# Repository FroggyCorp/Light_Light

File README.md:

# Light Light
It's a small PCB game with actually 2 games :

https://www.youtube.com/video/Cth2Q4qN7tQ/

https://www.youtube.com/video/z0U1Xu2ibLQ/

## The game

### How it work
Button 9 disable sound (horrible, i know)
Button 1 & 2 start game 1 or 2
All Button Player 1 & 2 at same time at the beggining reset highscore (little bit hard)

### Configuration
In light_light_func.h duree_jeu change the timeout of game1 2 = 20s
You can also change how many led will light at same time on game 1 with Jeu1_nombre_led_joueur_actif

### Game 1
You will have 4 LED, press button with led on as fast as you can until timeout of the game.

### Game 2
The program will add one led every x secondes, going faster and faster. It end when all the led are on for the two players.

## Game Board

Actually there is only dev board, which don't change so much. You can remove external connector to gain some place and make a smaller PCB.
It use an Attiny1604 & HT16K33A as it was the cheapest price and easy to use. Version with 75HC595 & 74HC595 may be a little bit cheaper but more difficult to make.
For Attiny1604, all reference on how to use it are[here]([https://pages.github.com/](https://github.com/SpenceKonde/AVR-Guidance/blob/master/UPDI/jtag2updi.md)) for UDPI & [here](https://github.com/SpenceKonde/megaTinyCore)
Thanks to [SpenceKonde](https://github.com/SpenceKonde) for his huge great work.

### Get notice
I use v1.1, v1.2 have some change and should work without problem.

### Information about the board
The board have 2 footprint for microphone, you need to get a passive one.
There are 2 foorprint for button + LED. One is cheap with standard 6x6mm tactil switch and 5730 LED, the other one use more expensive set with tactil switch & led in same package. You can take with [cap](https://www.lcsc.com/product-detail/Tactile-Switches_ROCPU-Switches-TPB01-101L1W_C2762125.html) or without and take that type of [cap] (https://www.lcsc.com/product-detail/Switch-Accessories-Caps_Khon-SC804AF1_C45359438.html). Be aware that some button + LED have cathode/anode at different position which will not work.
With 5730 LED, i recommend 5Kohm for R77 to R88 and 330ohm for the others.
You could also change the R for green LED.

### v1.2 :
- Correction Bug with Led J2 6-7-8-9
- Mutualising R for button
- Double footprint for microphone
- Change mounting hole
- Smaller PCB
- Add 5x220Ohm resistor to trick external battery cut off

## Small box

You can find .stl and FreeCad file inside FreeCad dir, as well as the PCB, i didn't try that version.

# Licence
Copyright (c) 2025 Froggy / FroggyCorp.

Do what you want with it until it's not money.

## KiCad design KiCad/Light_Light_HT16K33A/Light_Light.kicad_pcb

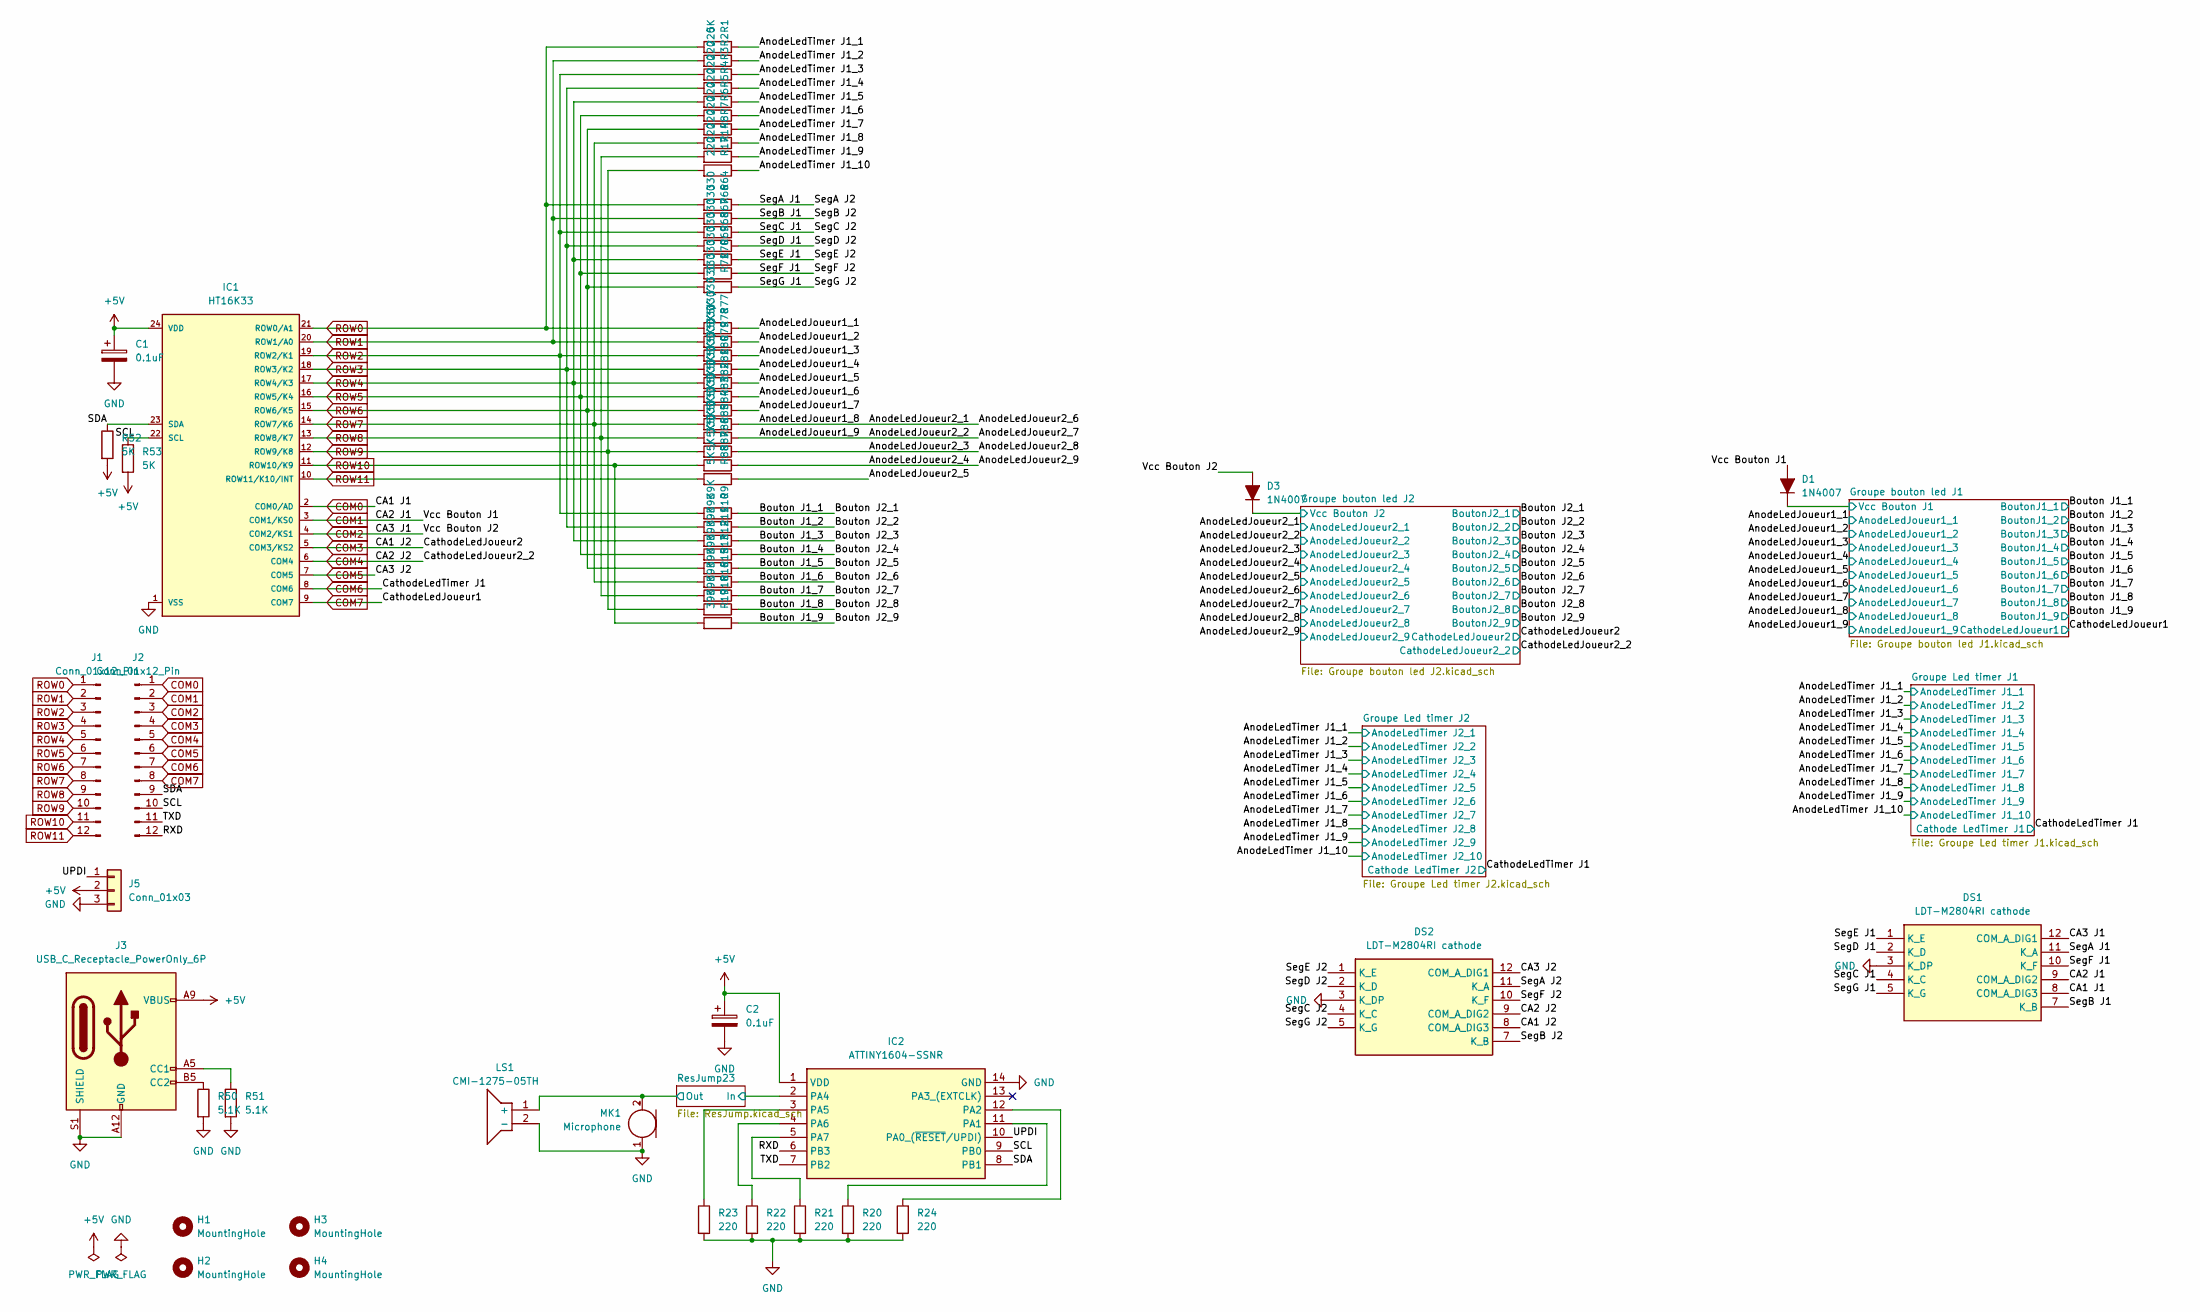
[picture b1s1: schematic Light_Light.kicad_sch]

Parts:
C1, C2: 0.1uF; C_0805_2012Metric_Pad1.15x1.40mm_HandSolder
D1, D3: 1N4007; D_DO-214AC_SMA; LCSC Part # C232439
DS1, DS2: LDT-M2804RI cathode; LDTM2804RI; Mouser Part Number 696-LDT-M2804RI
H1, H2, H3, H4: MountingHole; MountingHole_2.2mm_M2
IC1: HT16K33; LCSC Part # C5444736
IC2: ATTINY1604-SSNR; SOIC127P600X175-14N; Mouser Part Number 579-ATTINY1604-SSNR
J1, J2: Conn_01x12_Pin; PinHeader_1x12_P2.54mm_Vertical
J3: USB_C_Receptacle_PowerOnly_6P; USB_C_Receptacle_GCT_USB4125-xx-x_6P_TopMnt_Horizontal; LCSC Part # C668623
J5: Conn_01x03; PinHeader_1x03_P2.54mm_Horizontal; Part Number 1-0301FBV0T
LS1: CMI-1275-05TH; CMI127505TH; Mouser Part Number 179-CMI-1275-05TH
MK1: Microphone; POM-2244P-C3310-2-R; LCSC Part # C233957
R1, R52, R53: 5K; R_0805_2012Metric_Pad1.20x1.40mm_HandSolder
R2, R3, R4, R5, R6, R7, R8, R14, R17, R20, R21, R22, R23, R24: 220; R_0805_2012Metric_Pad1.20x1.40mm_HandSolder
R9, R10, R11, R12, R13, R15, R16, R18, R19: 39K; R_0805_2012Metric_Pad1.20x1.40mm_HandSolder
R50, R51: 5.1K; R_0805_2012Metric_Pad1.20x1.40mm_HandSolder
R64, R66, R67, R68, R69, R70, R71: 330; R_0805_2012Metric_Pad1.20x1.40mm_HandSolder
R77, R78, R79, R80, R81, R82, R83, R84, R85, R86, R87, R88: 5K / 330; R_0805_2012Metric_Pad1.20x1.40mm_HandSolder

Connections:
+5V: C1.1, C2.1, IC1.24 (VDD), IC2.1 (VDD), J3.A9 (VBUS), J3.B9 (VBUS), J5.2, R52.2, R53.2
/AnodeLedJoueur1_1: R77.1; also elsewhere on the board
/AnodeLedJoueur1_2: R78.1; also elsewhere on the board
/AnodeLedJoueur1_3: R79.1; also elsewhere on the board
/AnodeLedJoueur1_4: R80.1; also elsewhere on the board
/AnodeLedJoueur1_5: R81.1; also elsewhere on the board
/AnodeLedJoueur1_6: R82.1; also elsewhere on the board
/AnodeLedJoueur1_7: R83.1; also elsewhere on the board
/AnodeLedJoueur1_8: R84.1; also elsewhere on the board
/AnodeLedJoueur1_9: R85.1; also elsewhere on the board
/AnodeLedJoueur2_3: R86.1; also elsewhere on the board
/AnodeLedJoueur2_4: R87.1; also elsewhere on the board
/AnodeLedJoueur2_5: R88.1; also elsewhere on the board
/AnodeLedTimer J1_1: R1.1; also elsewhere on the board
/AnodeLedTimer J1_2: R2.1; also elsewhere on the board
/AnodeLedTimer J1_3: R3.1; also elsewhere on the board
/AnodeLedTimer J1_4: R4.1; also elsewhere on the board
/AnodeLedTimer J1_5: R5.1; also elsewhere on the board
/AnodeLedTimer J1_6: R6.1; also elsewhere on the board
/AnodeLedTimer J1_7: R7.1; also elsewhere on the board
/AnodeLedTimer J1_8: R8.1; also elsewhere on the board
/AnodeLedTimer J1_9: R14.1; also elsewhere on the board
/AnodeLedTimer J1_10: R17.1; also elsewhere on the board
/Bouton J1_1: R9.1; also elsewhere on the board
/Bouton J1_2: R10.1; also elsewhere on the board
/Bouton J1_3: R11.1; also elsewhere on the board
/Bouton J1_4: R12.1; also elsewhere on the board
/Bouton J1_5: R13.1; also elsewhere on the board
/Bouton J1_6: R15.1; also elsewhere on the board
/Bouton J1_7: R16.1; also elsewhere on the board
/Bouton J1_8: R18.1; also elsewhere on the board
/Bouton J1_9: R19.1; also elsewhere on the board
/Groupe bouton led J1/Vcc Bouton J1: D1.1 (K); also elsewhere on the board
/Groupe bouton led J2/Vcc Bouton J2: D3.1 (K); also elsewhere on the board
/RXD: IC2.6 (PB3), J2.12
/ResJump23/In: IC2.2 (PA4); also elsewhere on the board
/ResJump23/Out: LS1.1 (+), MK1.2 (+); also elsewhere on the board
/SCL: IC1.22 (SCL), IC2.9 (PB0), J2.10, R53.1
/SDA: IC1.23 (SDA), IC2.8 (PB1), J2.9, R52.1
/SegA J1: DS1.11 (K_A), DS2.11 (K_A), R64.1
/SegB J1: DS1.7 (K_B), DS2.7 (K_B), R66.1
/SegC J1: DS1.4 (K_C), DS2.4 (K_C), R67.1
/SegD J1: DS1.2 (K_D), DS2.2 (K_D), R68.1
/SegE J1: DS1.1 (K_E), DS2.1 (K_E), R69.1
/SegF J1: DS1.10 (K_F), DS2.10 (K_F), R70.1
/SegG J1: DS1.5 (K_G), DS2.5 (K_G), R71.1
/TXD: IC2.7 (PB2), J2.11
/UPDI: IC2.10 (PA0_(~RESET/UPDI)), J5.1
COM0: DS1.8 (COM_A_DIG3), IC1.2 (COM0/AD), J2.1
COM1: D1.2 (A), DS1.9 (COM_A_DIG2), IC1.3 (COM1/KS0), J2.2
COM2: D3.2 (A), DS1.12 (COM_A_DIG1), IC1.4 (COM2/KS1), J2.3
COM3: DS2.8 (COM_A_DIG3), IC1.5 (COM3/KS2), J2.4; also elsewhere on the board
COM4: DS2.9 (COM_A_DIG2), IC1.6 (COM4), J2.5; also elsewhere on the board
COM5: DS2.12 (COM_A_DIG1), IC1.7 (COM5), J2.6
COM6: IC1.8 (COM6), J2.7; also elsewhere on the board
COM7: IC1.9 (COM7), J2.8; also elsewhere on the board
GND: C1.2, C2.2, DS1.3 (K_DP), DS2.3 (K_DP), IC1.1 (VSS), IC2.14 (GND), J3.A12 (GND), J3.B12 (GND), J3.S1 (SHIELD), J5.3, LS1.2 (-), MK1.1 (-), R20.2, R21.2, R22.2, R23.2, R24.2, R50.2, R51.2
unnamed: IC2.11 (PA1), R20.1
unnamed: IC2.12 (PA2), R24.1
unnamed: IC2.3 (PA5), R23.1
unnamed: IC2.4 (PA6), R22.1
unnamed: IC2.5 (PA7), R21.1
unnamed: J3.A5 (CC1), R51.1
unnamed: J3.B5 (CC2), R50.1
ROW0: IC1.21 (ROW0/A1), J1.1, R1.2, R64.2, R77.2
ROW1: IC1.20 (ROW1/A0), J1.2, R2.2, R66.2, R78.2
ROW2: IC1.19 (ROW2/K1), J1.3, R3.2, R9.2, R67.2, R79.2
ROW3: IC1.18 (ROW3/K2), J1.4, R4.2, R10.2, R68.2, R80.2
ROW4: IC1.17 (ROW4/K3), J1.5, R5.2, R11.2, R69.2, R81.2
ROW5: IC1.16 (ROW5/K4), J1.6, R6.2, R12.2, R70.2, R82.2
ROW6: IC1.15 (ROW6/K5), J1.7, R7.2, R13.2, R71.2, R83.2
ROW7: IC1.14 (ROW7/K6), J1.8, R8.2, R15.2, R84.2
ROW8: IC1.13 (ROW8/K7), J1.9, R14.2, R16.2, R85.2
ROW9: IC1.12 (ROW9/K8), J1.10, R17.2, R18.2, R86.2
ROW10: IC1.11 (ROW10/K9), J1.11, R19.2, R87.2
ROW11: IC1.10 (ROW11/K10/INT), J1.12, R88.2

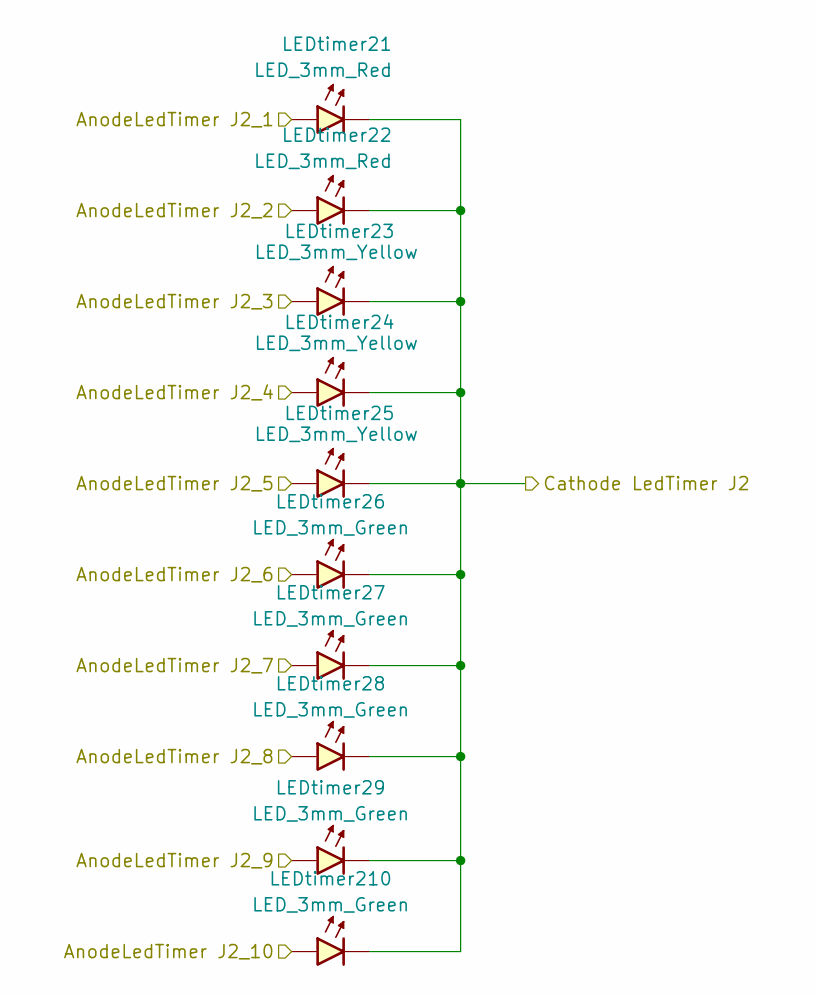
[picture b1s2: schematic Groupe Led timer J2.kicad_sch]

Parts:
LEDtimer21, LEDtimer22: LED_3mm_Red; LED_D3.0mm; LCSC Part # C84774
LEDtimer23, LEDtimer24, LEDtimer25: LED_3mm_Yellow; LED_D3.0mm; LCSC Part # C2895472
LEDtimer26, LEDtimer27, LEDtimer28, LEDtimer29, LEDtimer210: LED_3mm_Green; LED_D3.0mm; LCSC Part # C5907154

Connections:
/AnodeLedTimer J1_1: LEDtimer21.2 (A); also elsewhere on the board
/AnodeLedTimer J1_2: LEDtimer22.2 (A); also elsewhere on the board
/AnodeLedTimer J1_3: LEDtimer23.2 (A); also elsewhere on the board
/AnodeLedTimer J1_4: LEDtimer24.2 (A); also elsewhere on the board
/AnodeLedTimer J1_5: LEDtimer25.2 (A); also elsewhere on the board
/AnodeLedTimer J1_6: LEDtimer26.2 (A); also elsewhere on the board
/AnodeLedTimer J1_7: LEDtimer27.2 (A); also elsewhere on the board
/AnodeLedTimer J1_8: LEDtimer28.2 (A); also elsewhere on the board
/AnodeLedTimer J1_9: LEDtimer29.2 (A); also elsewhere on the board
/AnodeLedTimer J1_10: LEDtimer210.2 (A); also elsewhere on the board
COM6: LEDtimer21.1 (K), LEDtimer22.1 (K), LEDtimer23.1 (K), LEDtimer24.1 (K), LEDtimer25.1 (K), LEDtimer26.1 (K), LEDtimer27.1 (K), LEDtimer28.1 (K), LEDtimer29.1 (K), LEDtimer210.1 (K); also elsewhere on the board

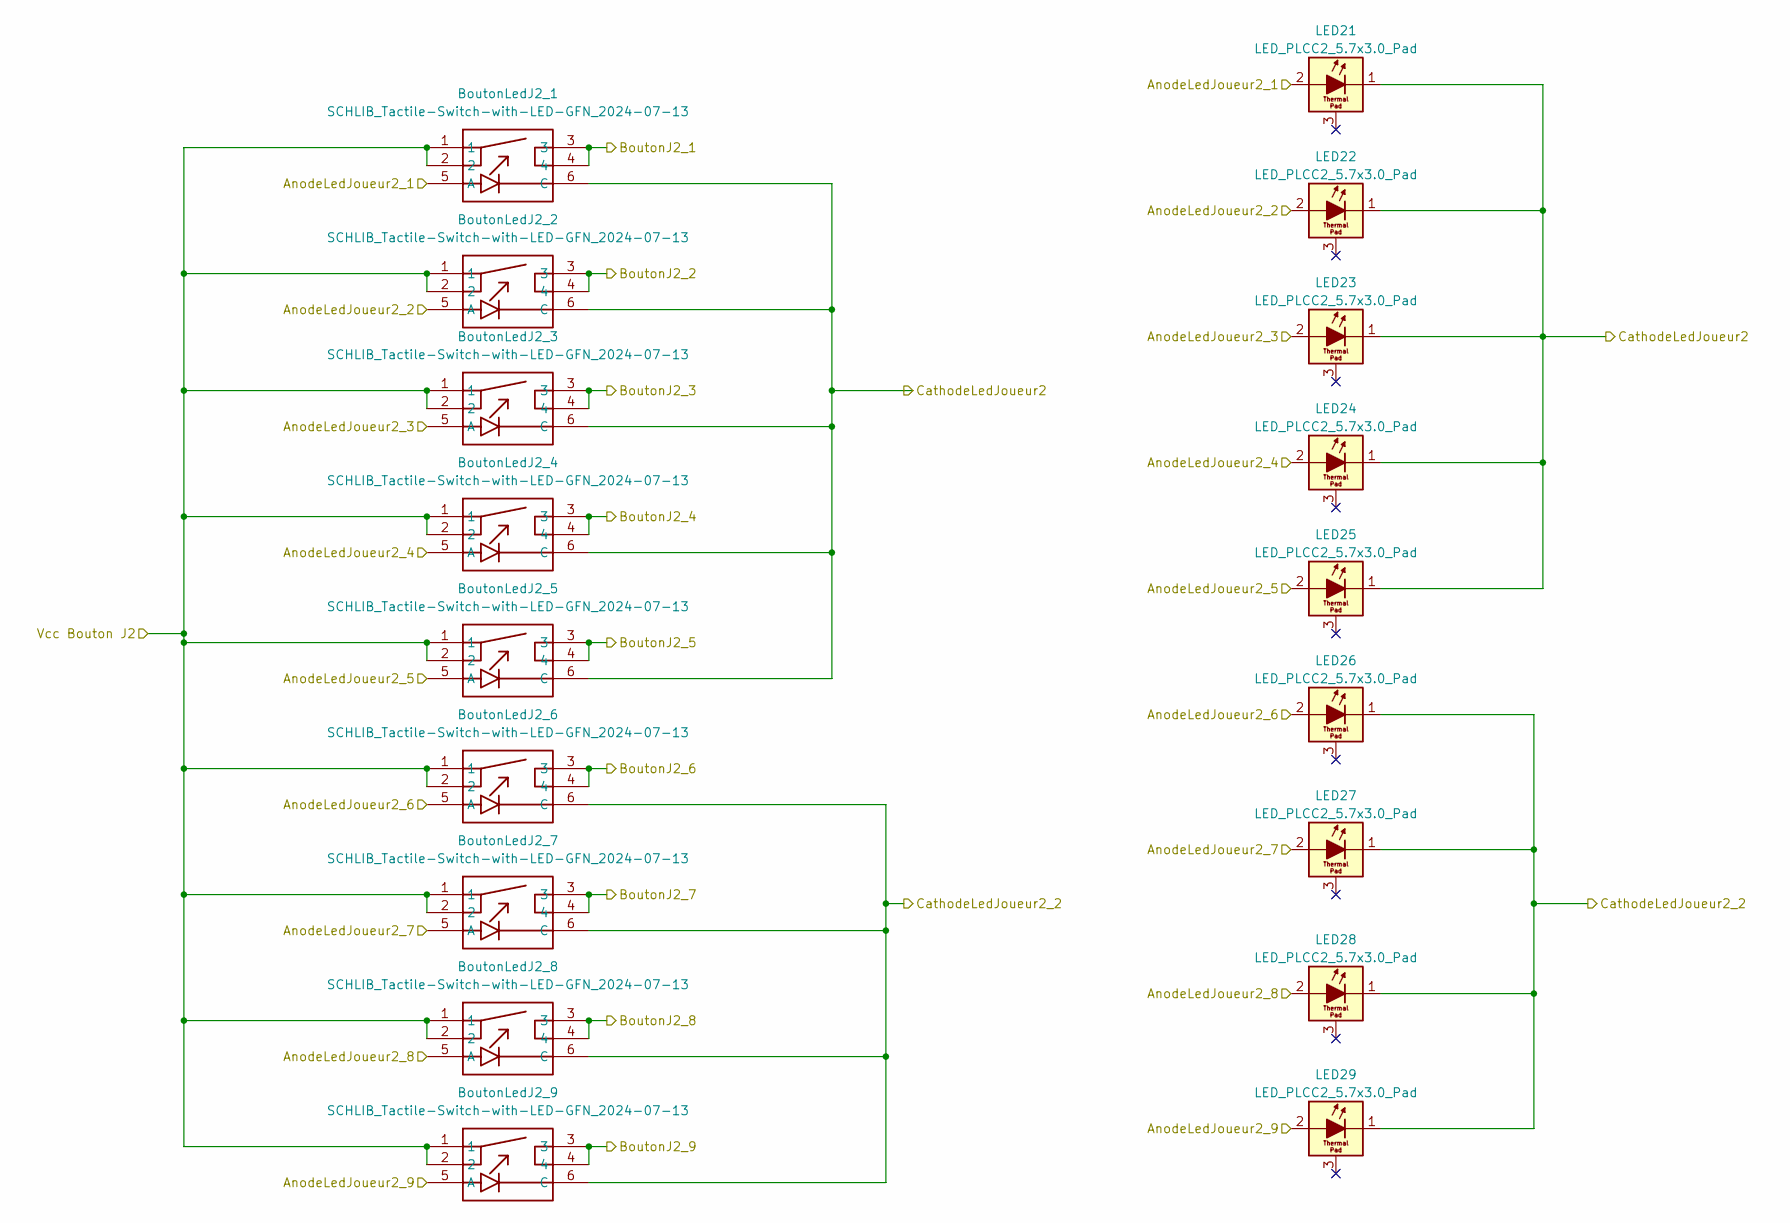
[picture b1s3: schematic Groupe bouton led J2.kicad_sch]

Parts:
BoutonLedJ2_1, BoutonLedJ2_2, BoutonLedJ2_3, BoutonLedJ2_4, BoutonLedJ2_5, BoutonLedJ2_6, BoutonLedJ2_7, BoutonLedJ2_8, BoutonLedJ2_9: SCHLIB_Tactile-Switch-with-LED-GFN_2024-07-13; 6MM SWITCH WITH LED GFN; Manufacturer Part New SchematicLib; LCSC Part # C354964
LED21, LED22, LED23, LED24, LED25, LED26, LED27, LED28, LED29: LED_PLCC2_5.7x3.0_Pad; LED_Yuji_5730

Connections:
/AnodeLedJoueur1_8: BoutonLedJ2_1.5 (A), BoutonLedJ2_6.5 (A), LED21.2 (A), LED26.2 (A); also elsewhere on the board
/AnodeLedJoueur1_9: BoutonLedJ2_2.5 (A), BoutonLedJ2_7.5 (A), LED22.2 (A), LED27.2 (A); also elsewhere on the board
/AnodeLedJoueur2_3: BoutonLedJ2_3.5 (A), BoutonLedJ2_8.5 (A), LED23.2 (A), LED28.2 (A); also elsewhere on the board
/AnodeLedJoueur2_4: BoutonLedJ2_4.5 (A), BoutonLedJ2_9.5 (A), LED24.2 (A), LED29.2 (A); also elsewhere on the board
/AnodeLedJoueur2_5: BoutonLedJ2_5.5 (A), LED25.2 (A); also elsewhere on the board
/Bouton J1_1: BoutonLedJ2_1.3, BoutonLedJ2_1.4; also elsewhere on the board
/Bouton J1_2: BoutonLedJ2_2.3, BoutonLedJ2_2.4; also elsewhere on the board
/Bouton J1_3: BoutonLedJ2_3.3, BoutonLedJ2_3.4; also elsewhere on the board
/Bouton J1_4: BoutonLedJ2_4.3, BoutonLedJ2_4.4; also elsewhere on the board
/Bouton J1_5: BoutonLedJ2_5.3, BoutonLedJ2_5.4; also elsewhere on the board
/Bouton J1_6: BoutonLedJ2_6.3, BoutonLedJ2_6.4; also elsewhere on the board
/Bouton J1_7: BoutonLedJ2_7.3, BoutonLedJ2_7.4; also elsewhere on the board
/Bouton J1_8: BoutonLedJ2_8.3, BoutonLedJ2_8.4; also elsewhere on the board
/Bouton J1_9: BoutonLedJ2_9.3, BoutonLedJ2_9.4; also elsewhere on the board
/Groupe bouton led J2/Vcc Bouton J2: BoutonLedJ2_1.1, BoutonLedJ2_1.2, BoutonLedJ2_2.1, BoutonLedJ2_2.2, BoutonLedJ2_3.1, BoutonLedJ2_3.2, BoutonLedJ2_4.1, BoutonLedJ2_4.2, BoutonLedJ2_5.1, BoutonLedJ2_5.2, BoutonLedJ2_6.1, BoutonLedJ2_6.2, BoutonLedJ2_7.1, BoutonLedJ2_7.2, BoutonLedJ2_8.1, BoutonLedJ2_8.2, BoutonLedJ2_9.1, BoutonLedJ2_9.2; also elsewhere on the board
COM3: BoutonLedJ2_1.6 (C), BoutonLedJ2_2.6 (C), BoutonLedJ2_3.6 (C), BoutonLedJ2_4.6 (C), BoutonLedJ2_5.6 (C), LED21.1 (K), LED22.1 (K), LED23.1 (K), LED24.1 (K), LED25.1 (K); also elsewhere on the board
COM4: BoutonLedJ2_6.6 (C), BoutonLedJ2_7.6 (C), BoutonLedJ2_8.6 (C), BoutonLedJ2_9.6 (C), LED26.1 (K), LED27.1 (K), LED28.1 (K), LED29.1 (K); also elsewhere on the board

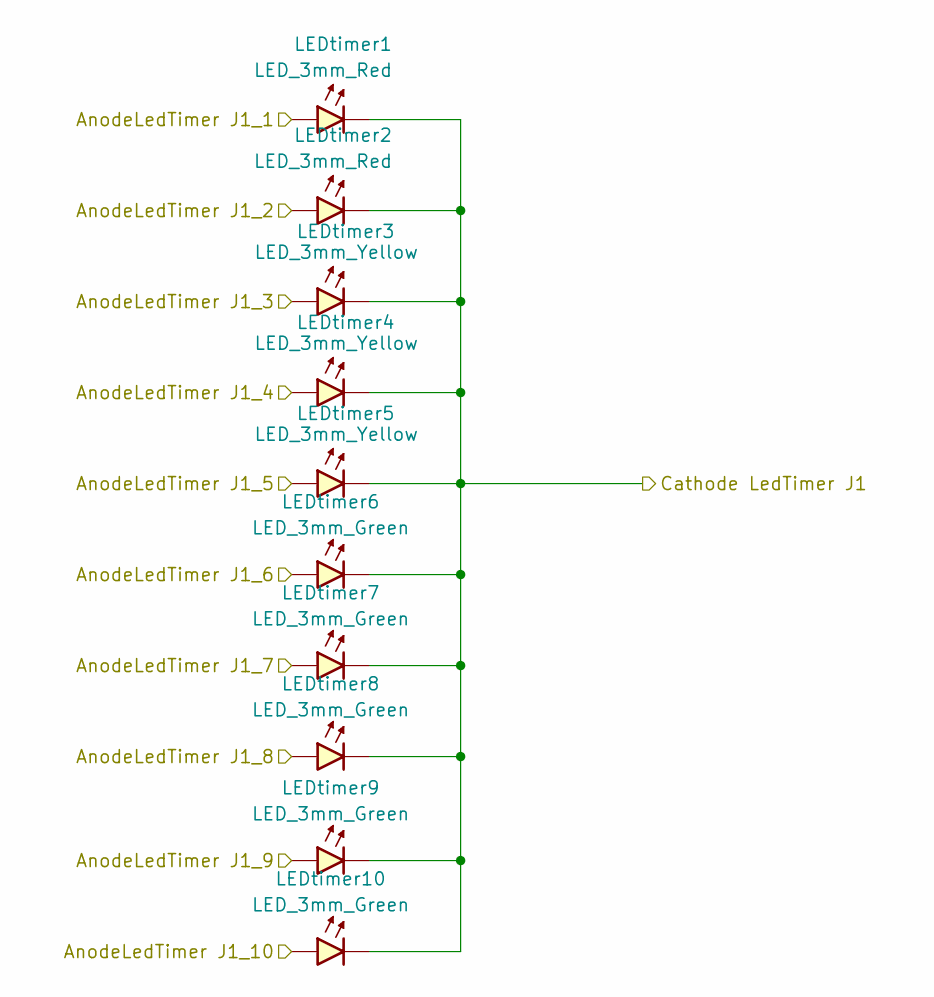
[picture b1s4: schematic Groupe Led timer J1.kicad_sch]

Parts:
LEDtimer1, LEDtimer2: LED_3mm_Red; LED_D3.0mm; LCSC Part # C84774
LEDtimer3, LEDtimer4, LEDtimer5: LED_3mm_Yellow; LED_D3.0mm; LCSC Part # C2895472
LEDtimer6, LEDtimer7, LEDtimer8, LEDtimer9, LEDtimer10: LED_3mm_Green; LED_D3.0mm; LCSC Part # C5907154

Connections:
/AnodeLedTimer J1_1: LEDtimer1.2 (A); also elsewhere on the board
/AnodeLedTimer J1_2: LEDtimer2.2 (A); also elsewhere on the board
/AnodeLedTimer J1_3: LEDtimer3.2 (A); also elsewhere on the board
/AnodeLedTimer J1_4: LEDtimer4.2 (A); also elsewhere on the board
/AnodeLedTimer J1_5: LEDtimer5.2 (A); also elsewhere on the board
/AnodeLedTimer J1_6: LEDtimer6.2 (A); also elsewhere on the board
/AnodeLedTimer J1_7: LEDtimer7.2 (A); also elsewhere on the board
/AnodeLedTimer J1_8: LEDtimer8.2 (A); also elsewhere on the board
/AnodeLedTimer J1_9: LEDtimer9.2 (A); also elsewhere on the board
/AnodeLedTimer J1_10: LEDtimer10.2 (A); also elsewhere on the board
COM6: LEDtimer1.1 (K), LEDtimer2.1 (K), LEDtimer3.1 (K), LEDtimer4.1 (K), LEDtimer5.1 (K), LEDtimer6.1 (K), LEDtimer7.1 (K), LEDtimer8.1 (K), LEDtimer9.1 (K), LEDtimer10.1 (K); also elsewhere on the board

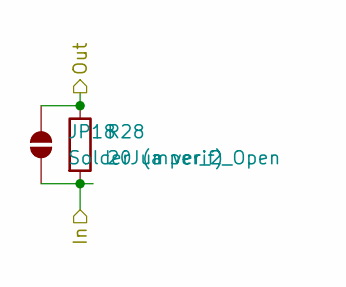
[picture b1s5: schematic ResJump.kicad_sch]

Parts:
JP18: SolderJumper_2_Open; SolderJumper-2_P1.3mm_Open_Pad1.0x1.5mm
R28: 20 (a verif); R_0805_2012Metric_Pad1.20x1.40mm_HandSolder

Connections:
/ResJump23/In: JP18.2 (B), R28.2; also elsewhere on the board
/ResJump23/Out: JP18.1 (A), R28.1; also elsewhere on the board

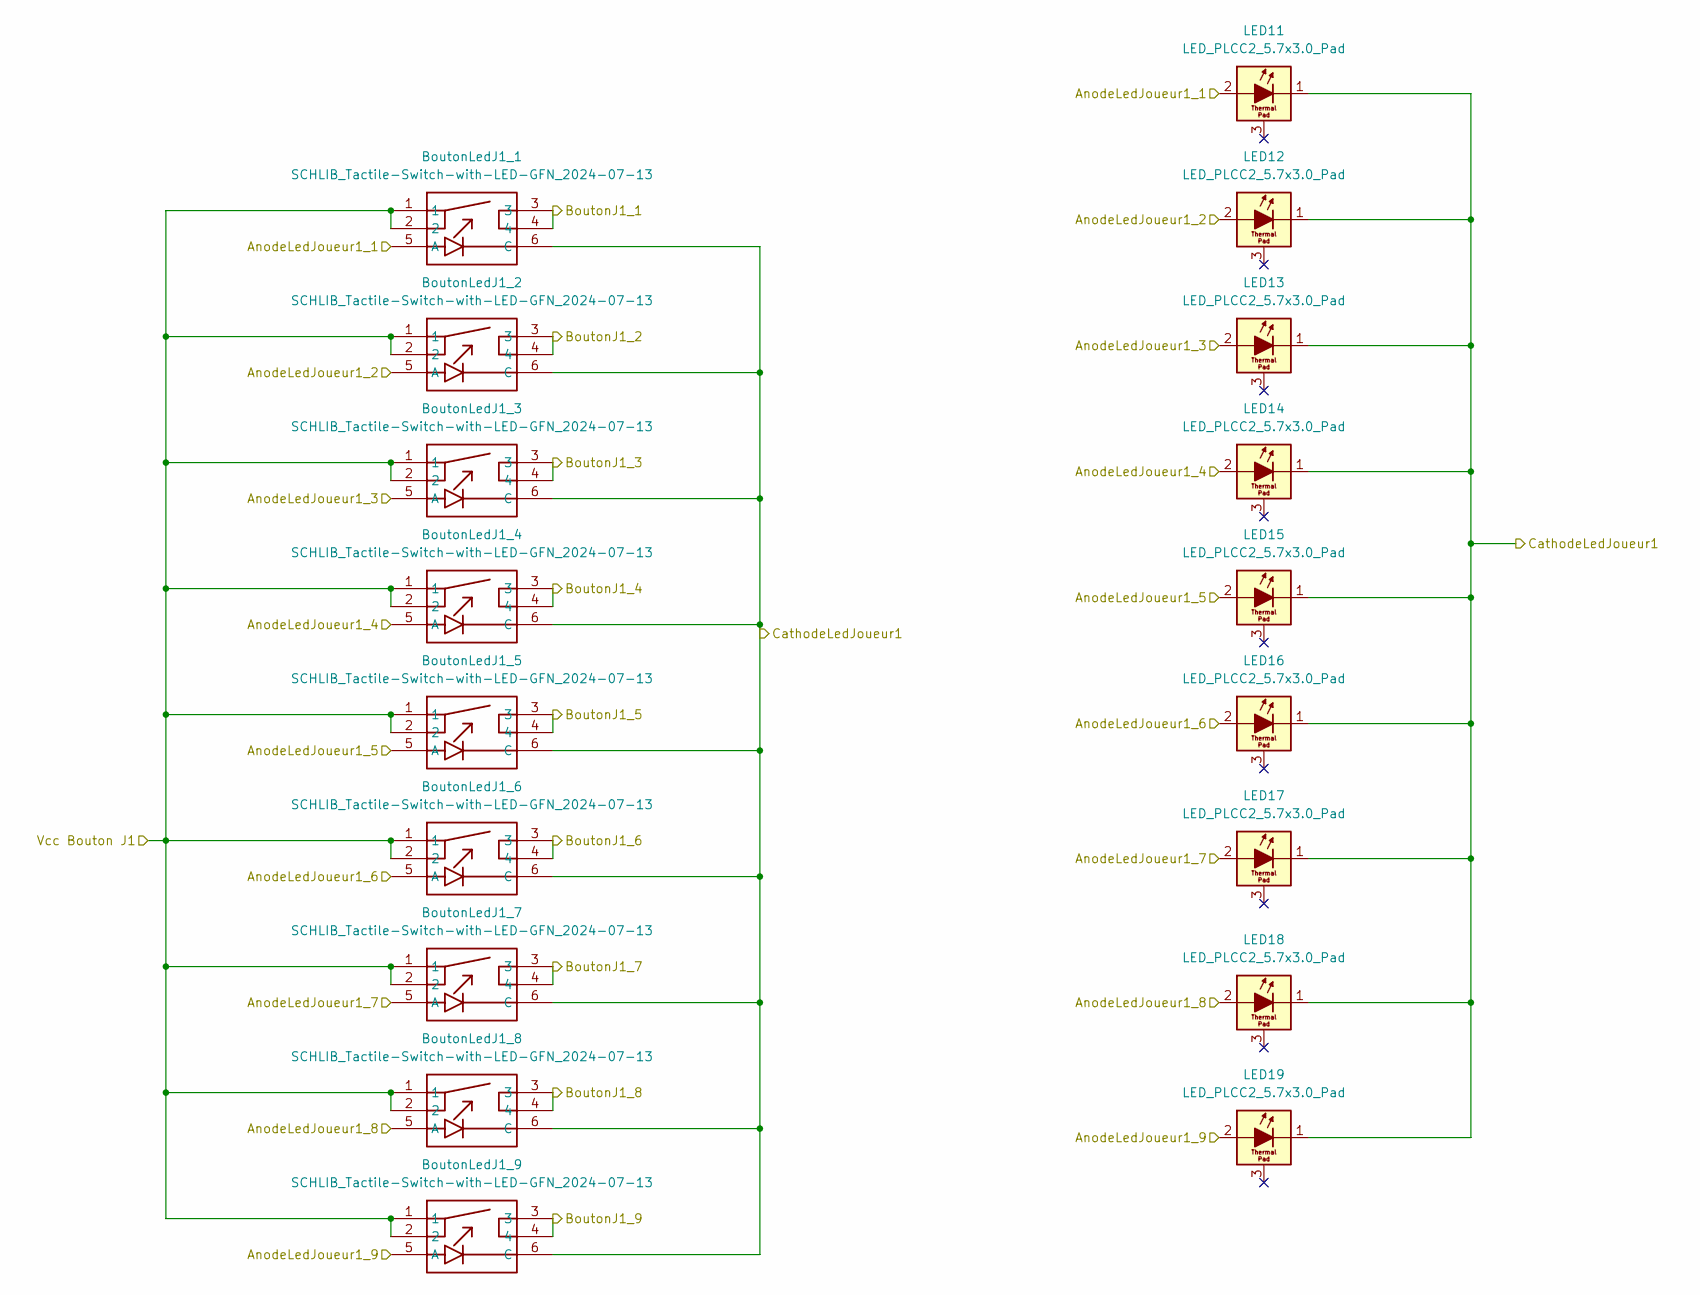
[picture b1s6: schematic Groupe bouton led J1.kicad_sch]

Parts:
BoutonLedJ1_1, BoutonLedJ1_2, BoutonLedJ1_3, BoutonLedJ1_4, BoutonLedJ1_5, BoutonLedJ1_6, BoutonLedJ1_7, BoutonLedJ1_8, BoutonLedJ1_9: SCHLIB_Tactile-Switch-with-LED-GFN_2024-07-13; 6MM SWITCH WITH LED GFN; Manufacturer Part New SchematicLib; LCSC Part # C354964
LED11, LED12, LED13, LED14, LED15, LED16, LED17, LED18, LED19: LED_PLCC2_5.7x3.0_Pad; LED_Yuji_5730

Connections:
/AnodeLedJoueur1_1: BoutonLedJ1_1.5 (A), LED11.2 (A); also elsewhere on the board
/AnodeLedJoueur1_2: BoutonLedJ1_2.5 (A), LED12.2 (A); also elsewhere on the board
/AnodeLedJoueur1_3: BoutonLedJ1_3.5 (A), LED13.2 (A); also elsewhere on the board
/AnodeLedJoueur1_4: BoutonLedJ1_4.5 (A), LED14.2 (A); also elsewhere on the board
/AnodeLedJoueur1_5: BoutonLedJ1_5.5 (A), LED15.2 (A); also elsewhere on the board
/AnodeLedJoueur1_6: BoutonLedJ1_6.5 (A), LED16.2 (A); also elsewhere on the board
/AnodeLedJoueur1_7: BoutonLedJ1_7.5 (A), LED17.2 (A); also elsewhere on the board
/AnodeLedJoueur1_8: BoutonLedJ1_8.5 (A), LED18.2 (A); also elsewhere on the board
/AnodeLedJoueur1_9: BoutonLedJ1_9.5 (A), LED19.2 (A); also elsewhere on the board
/Bouton J1_1: BoutonLedJ1_1.3, BoutonLedJ1_1.4; also elsewhere on the board
/Bouton J1_2: BoutonLedJ1_2.3, BoutonLedJ1_2.4; also elsewhere on the board
/Bouton J1_3: BoutonLedJ1_3.3, BoutonLedJ1_3.4; also elsewhere on the board
/Bouton J1_4: BoutonLedJ1_4.3, BoutonLedJ1_4.4; also elsewhere on the board
/Bouton J1_5: BoutonLedJ1_5.3, BoutonLedJ1_5.4; also elsewhere on the board
/Bouton J1_6: BoutonLedJ1_6.3, BoutonLedJ1_6.4; also elsewhere on the board
/Bouton J1_7: BoutonLedJ1_7.3, BoutonLedJ1_7.4; also elsewhere on the board
/Bouton J1_8: BoutonLedJ1_8.3, BoutonLedJ1_8.4; also elsewhere on the board
/Bouton J1_9: BoutonLedJ1_9.3, BoutonLedJ1_9.4; also elsewhere on the board
/Groupe bouton led J1/Vcc Bouton J1: BoutonLedJ1_1.1, BoutonLedJ1_1.2, BoutonLedJ1_2.1, BoutonLedJ1_2.2, BoutonLedJ1_3.1, BoutonLedJ1_3.2, BoutonLedJ1_4.1, BoutonLedJ1_4.2, BoutonLedJ1_5.1, BoutonLedJ1_5.2, BoutonLedJ1_6.1, BoutonLedJ1_6.2, BoutonLedJ1_7.1, BoutonLedJ1_7.2, BoutonLedJ1_8.1, BoutonLedJ1_8.2, BoutonLedJ1_9.1, BoutonLedJ1_9.2; also elsewhere on the board
COM7: BoutonLedJ1_1.6 (C), BoutonLedJ1_2.6 (C), BoutonLedJ1_3.6 (C), BoutonLedJ1_4.6 (C), BoutonLedJ1_5.6 (C), BoutonLedJ1_6.6 (C), BoutonLedJ1_7.6 (C), BoutonLedJ1_8.6 (C), BoutonLedJ1_9.6 (C), LED11.1 (K), LED12.1 (K), LED13.1 (K), LED14.1 (K), LED15.1 (K), LED16.1 (K), LED17.1 (K), LED18.1 (K), LED19.1 (K); also elsewhere on the board

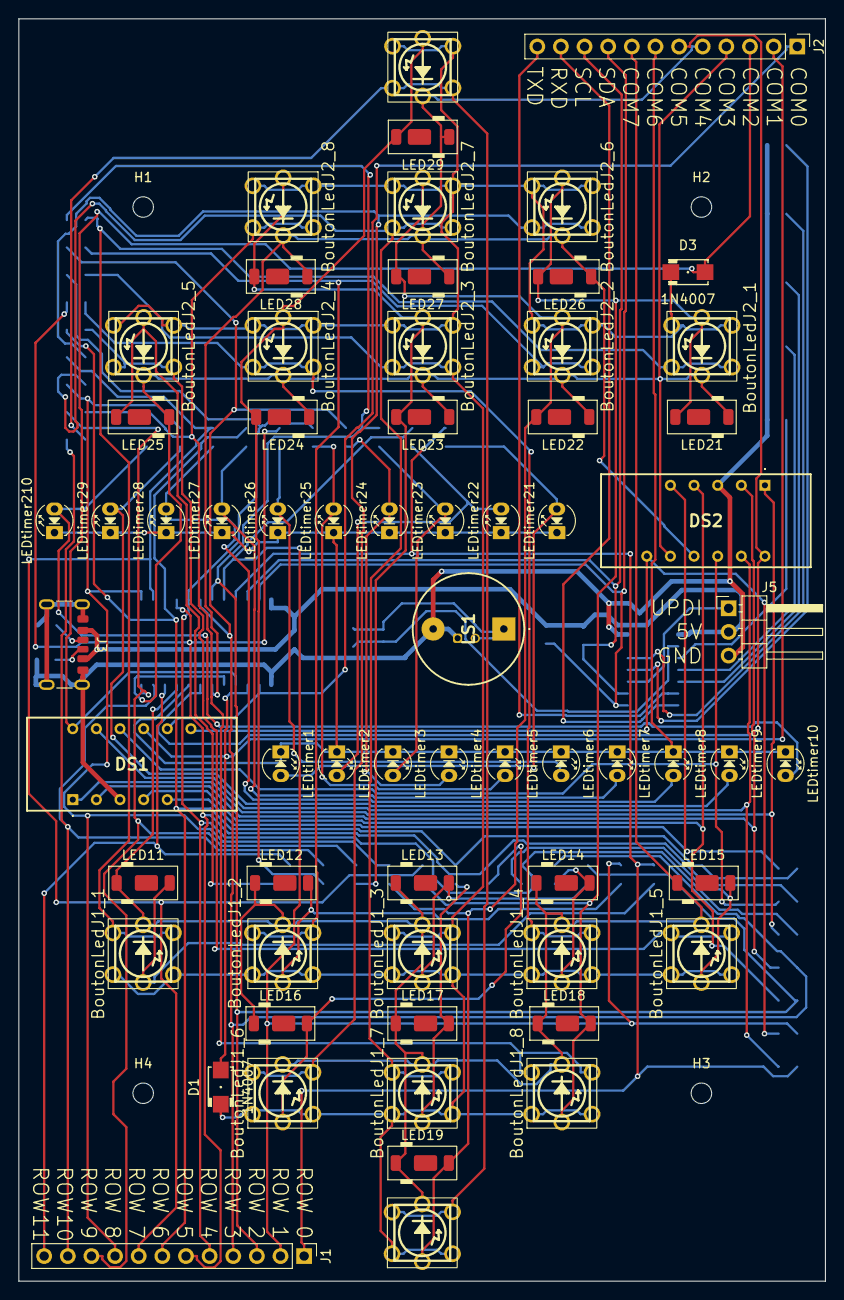
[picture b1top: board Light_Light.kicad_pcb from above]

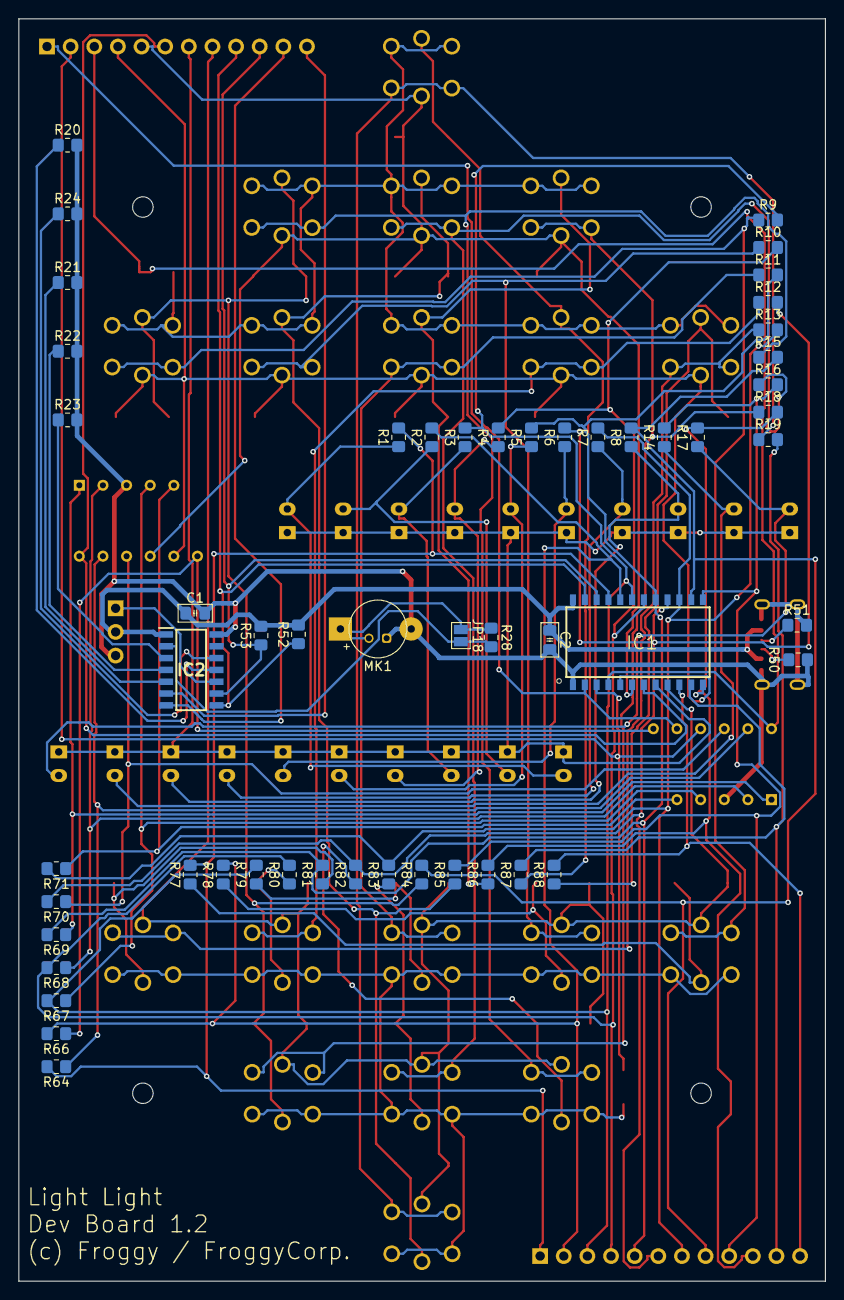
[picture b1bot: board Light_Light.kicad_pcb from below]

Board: 2 copper layers, 86.7 x 135.7 mm, 123 parts (54 on the bottom side), 76 nets.

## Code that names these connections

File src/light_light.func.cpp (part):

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}

void tricking_external_battery() {
    pinMode(PIN_PA1, OUTPUT);
    pinMode(PIN_PA2, OUTPUT);
    pinMode(PIN_PA5, OUTPUT);
    pinMode(PIN_PA6, OUTPUT);
    pinMode(PIN_PA7, OUTPUT);

    if (((millis() - timer_tricking_external_battery) > TRICKING_EXTERNAL_BATTERY_ON) && (state_tricking_external_battery == HIGH)) {
        digitalWrite(PIN_PA1, LOW);
        digitalWrite(PIN_PA5, LOW);
        digitalWrite(PIN_PA6, LOW);
        digitalWrite(PIN_PA7, LOW);
        state_tricking_external_battery = LOW;
        timer_tricking_external_battery = millis();
    }
    
    if (((millis() - timer_tricking_external_battery) > TRICKING_EXTERNAL_BATTERY_OFF) && (state_tricking_external_battery == LOW)) {
        digitalWrite(PIN_PA1, HIGH);
        digitalWrite(PIN_PA5, HIGH);
        digitalWrite(PIN_PA6, HIGH);
        digitalWrite(PIN_PA7, HIGH);
        state_tricking_external_battery = HIGH;
        timer_tricking_external_battery = millis();
    }
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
